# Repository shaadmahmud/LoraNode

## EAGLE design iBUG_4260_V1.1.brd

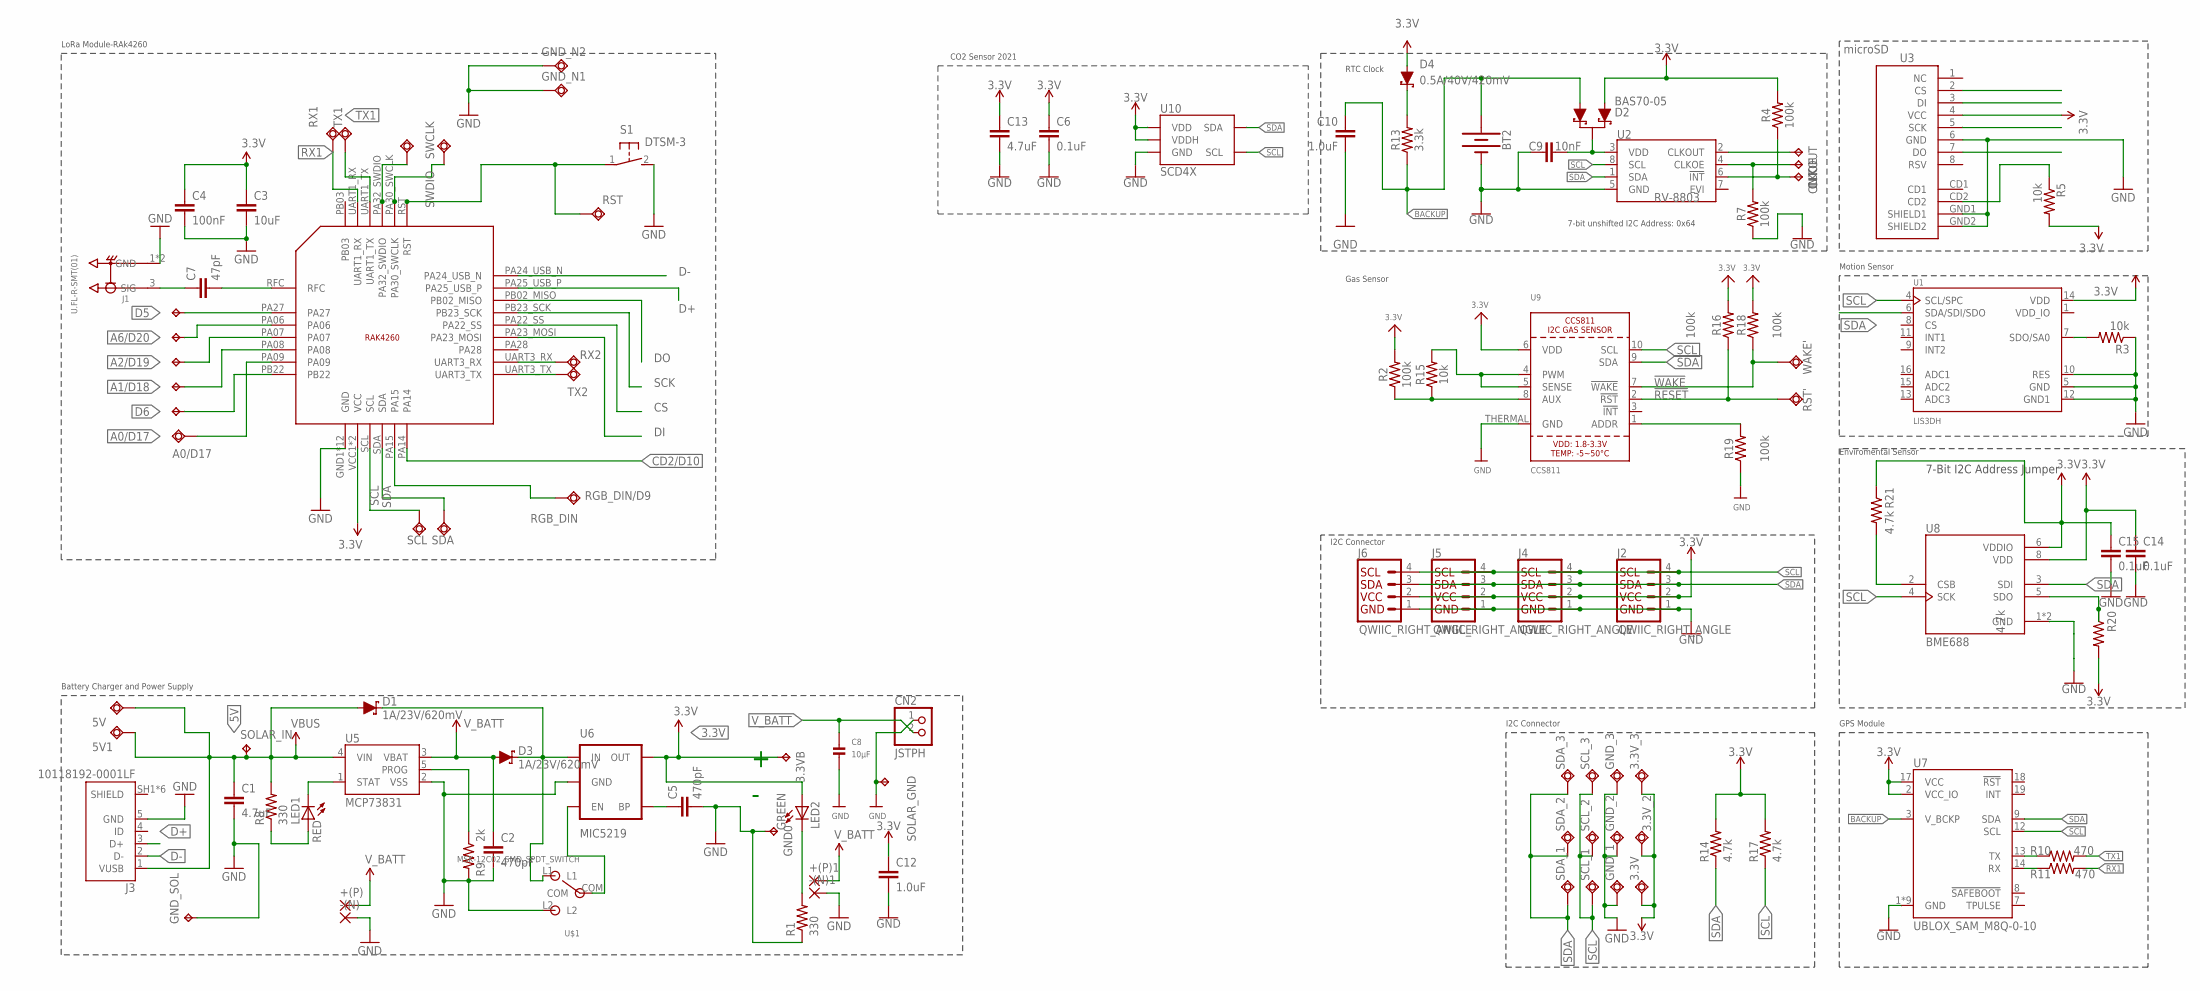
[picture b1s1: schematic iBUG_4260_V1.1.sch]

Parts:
3.3V, 3.3V_2, 3.3V_3: TPSQTP15R; TP15R
3.3VB: TPTP12SQ; TP12SQ
5V, 5V1: TPSQTP19R; TP19R
+(P), +(P)1: SMD2; SMD1,27-2,54
-(N), -(N)1: SMD2; SMD1,27-2,54
A0/D17: TPSQTP15R; TP15R
BT2: BATTERY-12MM_SMD; BATTCON_12MM
C1: 4.7uF; 0402-CAP
C2, C5: 470pF; 0402-CAP
C3: 10uF; 0402-CAP
C4: 100nF; 0402-CAP
C6, C14, C15: 0.1uF; 0603
C7: 47pF; 0402-CAP
C8: 10µF; 0805
C9: 10nF; 0603
C10, C12: 1.0uF; 0603
C13: 4.7uF; 0603
CLKOE: TPTP12R; TP12R
CLKOUT: TPTP12R; TP12R
CN2: JSTPH; JSTPH2
D1, D3: 1A/23V/620mV; SOD-323
D2: BAS70-05; SOT23-3
D4: 0.5A/40V/420mV; SOD-323
GND0: TPTP12SQ; TP12SQ
GND_1, GND_2, GND_3: TPSQTP15R; TP15R
GND_N1, GND_N2: TPSQTP19R; TP19R
GND_SOL: TPTP12SQ; TP12SQ
INT: TPTP12R; TP12R
J1: U.FL-R-SMT(01); HRS_U.FL-R-SMT(01)
J2, J4, J5, J6: QWIIC_RIGHT_ANGLE; JST04_1MM_RA
J3: 10118192-0001LF; AMPHENOL_10118192-0001LF
LED1: RED; LED-0603@1
LED2: GREEN; LED-0603@1
P0.1: TP5P5-25-13; P5-25-13
R1, R8: 330; 0402-RES
R2, R16, R18, R19: 100k; 0603@3
R3, R5: 10k; 0603-RES
R4, R7: 100k; 0603@2
R9: 2k; 0603-RES
R10, R11: 470; 0603@3
R13: 3.3k; 0603@3
R14, R17: 4.7k; 0402-RES
R15: 10k; 0603@3
R20, R21: 4.7k; 0603@1
RGB_DIN/D9: TPSQTP15R; TP15R
RST: TPSQTP19R; TP19R
RST': TPSQTP15R; TP15R
RX1, RX2: TPSQTP15R; TP15R
S1: DTSM-3
SCL: TPSQTP15R; TP15R
SCL_1, SCL_2, SCL_3: TPSQTP15R; TP15R
SDA: TPSQTP15R; TP15R
SDA_1, SDA_2, SDA_3: TPSQTP15R; TP15R
SOLAR_GND: TPTP20SQ; TP20SQ
SOLAR_IN: TPTP20SQ; TP20SQ
SWCLK: TPSQTP19R; TP19R
SWDIO: TPSQTP18R; TP18R
TX1, TX2: TPSQTP15R; TP15R
U1: LIS3DH; PQFN50P300X300X100-16N
U2: RV-8803; RV-3028
U3: microSD; MICRO-SD-SOCKET-PP
U5: MCP73831; SOT23-5
U6: MIC5219; SOT23-5
U7: UBLOX_SAM_M8Q-0-10; SAM-M8Q
U8: BME688; IC_BME688
U9: CCS811
U10: SCD4X
U$1: MSK-12C02_SMD_SPDT_SWITCH; MSK-12C02
U$3: RAK4260
WAKE': TPSQTP15R; TP15R

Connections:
3.3V: 3.3V.TP, 3.3VB.TP, 3.3V_2.TP, 3.3V_3.TP, C3.1, C4.1, C6.1, C12.1, C13.1, C14.1, C15.1, D2.1 (A), D4.A, J2.2, J4.2, J5.2, J6.2, LED2.A, R2.2, R4.2, R5.2, R14.2, R16.2, R17.2, R18.2, R20.2, R21.1, U1.14 (VDD), U3.4 (VCC), U6.5 (OUT), U7.2 (VCC_IO), U7.17 (VCC), U8.6 (VDDIO), U8.8 (VDD), U9.6 (VDD), U10.7 (VDD), U10.19 (VDDH), U$3.VCC1 (VCC), U$3.VCC2 (VCC)
5V: 5V.TP, 5V1.TP, C1.1, D1.A, J3.1 (VUSB), R8.2, SOLAR_IN.TP, U5.4 (VIN)
!INT: INT.TP, R4.1, U2.6 (!INT)
!RESET: R16.1, RST'.TP, U9.2 (!RST)
!WAKE: R18.1, U9.7 (!WAKE), WAKE'.TP
A0/D17: A0/D17.TP, U$3.PA09
A1/D18: P0.1.TP-2, U$3.PA08
A2/D19: P0.1.TP-3, U$3.PA07
A6/D20: P0.1.TP-4, U$3.PA06
BACKUP: BT2.PWR@1 (+), C10.1, D2.2 (A1), R13.1, U7.3 (V_BCKP)
CD1: R5.1, U3.CD2
CD2/D10: U$3.PA14
CLKOE: CLKOE.TP, R7.2, U2.4 (CLKOE)
CLKOUT: CLKOUT.TP, U2.2 (CLKOUT)
CS: U3.2 (CS), U$3.PA22_SS
D5: P0.1.TP-5, U$3.PA27
D6: P0.1.TP-1, U$3.PB22
D+: J3.3 (D+), U$3.PA25_USB_P
D-: J3.2 (D-), U$3.PA24_USB_N
DI: U3.3 (DI), U$3.PA23_MOSI
DO: U3.7 (DO), U$3.PB02_MISO
GND: -(N).1, -(N)1.1, BT2.GND (-), C1.2, C2.2, C3.2, C4.2, C5.2, C6.2, C8.2, C9.1, C10.2, C12.2, C13.2, C14.2, C15.2, CN2.1, GND0.TP, GND_1.TP, GND_2.TP, GND_3.TP, GND_N1.TP, GND_N2.TP, GND_SOL.TP, J1.1 (GND), J1.2 (GND), J2.1, J3.5 (GND), J4.1, J5.1, J6.1, R1.1, R3.1, R7.1, R9.2, R19.1, S1.2, SOLAR_GND.TP, U1.5 (GND), U1.10 (RES), U1.12 (GND1), U2.5 (GND), U3.6 (GND), U3.GND1 (SHIELD1), U3.GND2 (SHIELD2), U5.2 (VSS), U6.2 (GND), U7.1 (GND), U7.4 (GND), U7.5 (GND), U7.6 (GND), U7.10 (GND), U7.11 (GND), U7.15 (GND), U7.16 (GND), U7.20 (GND), U8.1 (GND), U8.7 (GND), U9.THERMAL (GND), U10.6 (GND), U10.20 (GND), U10.CP (GND), U$1.L2, U$3.GND1 (GND), U$3.GND3 (GND), U$3.GND10 (GND), U$3.GND17 (GND), U$3.GND18 (GND), U$3.GND28 (GND), U$3.GND35 (GND), U$3.GND36 (GND), U$3.GND37 (GND), U$3.GND38 (GND), U$3.GND39 (GND), U$3.GND40 (GND)
unnamed: LED2.C, R1.2
unnamed: D1.C, D3.C, U6.1 (IN), U$1.L1
unnamed: C7.1, J1.3 (SIG)
unnamed: R9.1, U5.5 (PROG)
unnamed: U6.3 (EN), U$1.COM
unnamed: C7.2, U$3.RFC
unnamed: C9.2, D2.3 (C), U2.3 (VDD)
unnamed: SWDIO.TP, U$3.PA32_SWDIO
unnamed: R15.2, U9.4 (PWM), U9.5 (SENSE)
unnamed: R2.1, R15.1, U9.8 (AUX)
unnamed: LED1.A, R8.1
unnamed: LED1.C, U5.1 (STAT)
unnamed: R19.2, U9.1 (ADDR)
unnamed: C5.1, U6.4 (BP)
unnamed: RX2.TP, U$3.UART3_RX
unnamed: R3.2, U1.7 (SDO/SA0)
unnamed: SWCLK.TP, U$3.PA30_SWCLK
unnamed: R20.1, U8.5 (SDO)
unnamed: TX2.TP, U$3.UART3_TX
unnamed: D4.C, R13.2
unnamed: R21.2, U8.2 (CSB)
RGB_DIN: RGB_DIN/D9.TP, U$3.PA15
RST: RST.TP, S1.1, U$3.RST
RX1: R11.2, RX1.TP, U$3.UART1_RX
RXLV: R11.1, U7.14 (RX)
SCK: U3.5 (SCK), U$3.PB23_SCK
SCL: J2.4, J4.4, J5.4, J6.4, R17.1, SCL.TP, SCL_1.TP, SCL_2.TP, SCL_3.TP, U1.4 (SCL/SPC), U2.8 (SCL), U7.12 (SCL), U8.4 (SCK), U9.10 (SCL), U10.9 (SCL), U$3.SCL
SDA: J2.3, J4.3, J5.3, J6.3, R14.1, SDA.TP, SDA_1.TP, SDA_2.TP, SDA_3.TP, U1.6 (SDA/SDI/SDO), U2.1 (SDA), U7.9 (SDA), U8.3 (SDI), U9.9 (SDA), U10.10 (SDA), U$3.SDA
TX1: R10.2, TX1.TP, U$3.UART1_TX
TXLV: R10.1, U7.13 (TX)
VDD_IO: U1.1 (VDD_IO)
V_BATT: +(P).1, +(P)1.1, C2.1, C8.1, CN2.2, D3.A, U5.3 (VBAT)

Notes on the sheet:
Battery Charger and Power Supply
7-bit unshifted I2C Address: 0x64
7-Bit I2C Address Jumper
GPS Module
Enviromental Sensor
Motion Sensor
I2C Connector
RTC Clock
LoRa Module-RAk4260
CO2 Sensor 2021
Gas Sensor

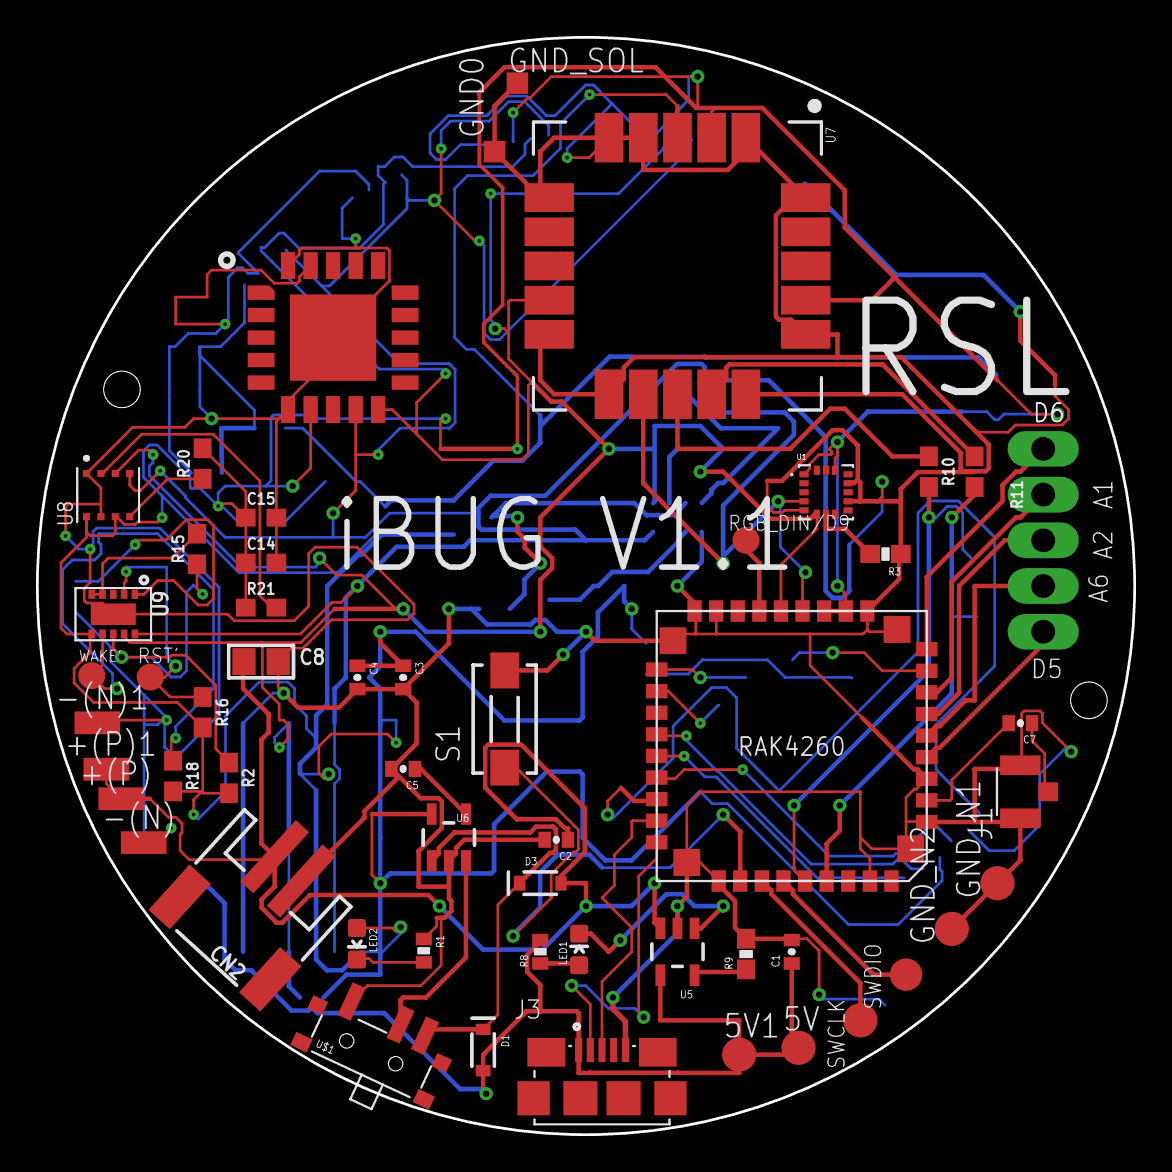
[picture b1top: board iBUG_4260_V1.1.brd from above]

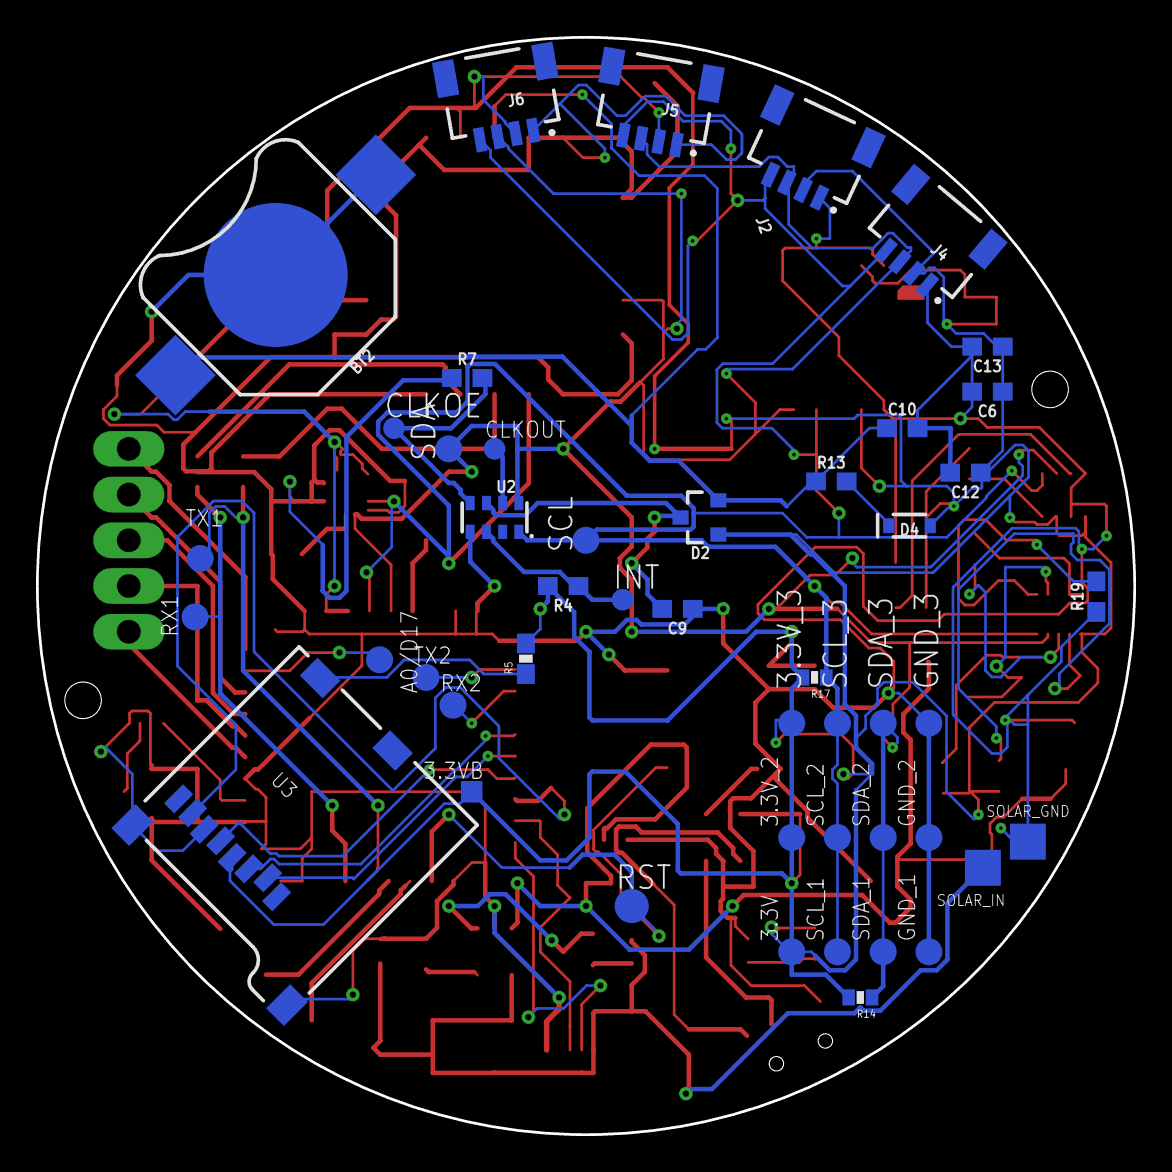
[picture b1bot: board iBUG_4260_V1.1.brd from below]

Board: 2 copper layers, 61.0 x 61.0 mm, 101 parts (47 on the bottom side), 52 nets.

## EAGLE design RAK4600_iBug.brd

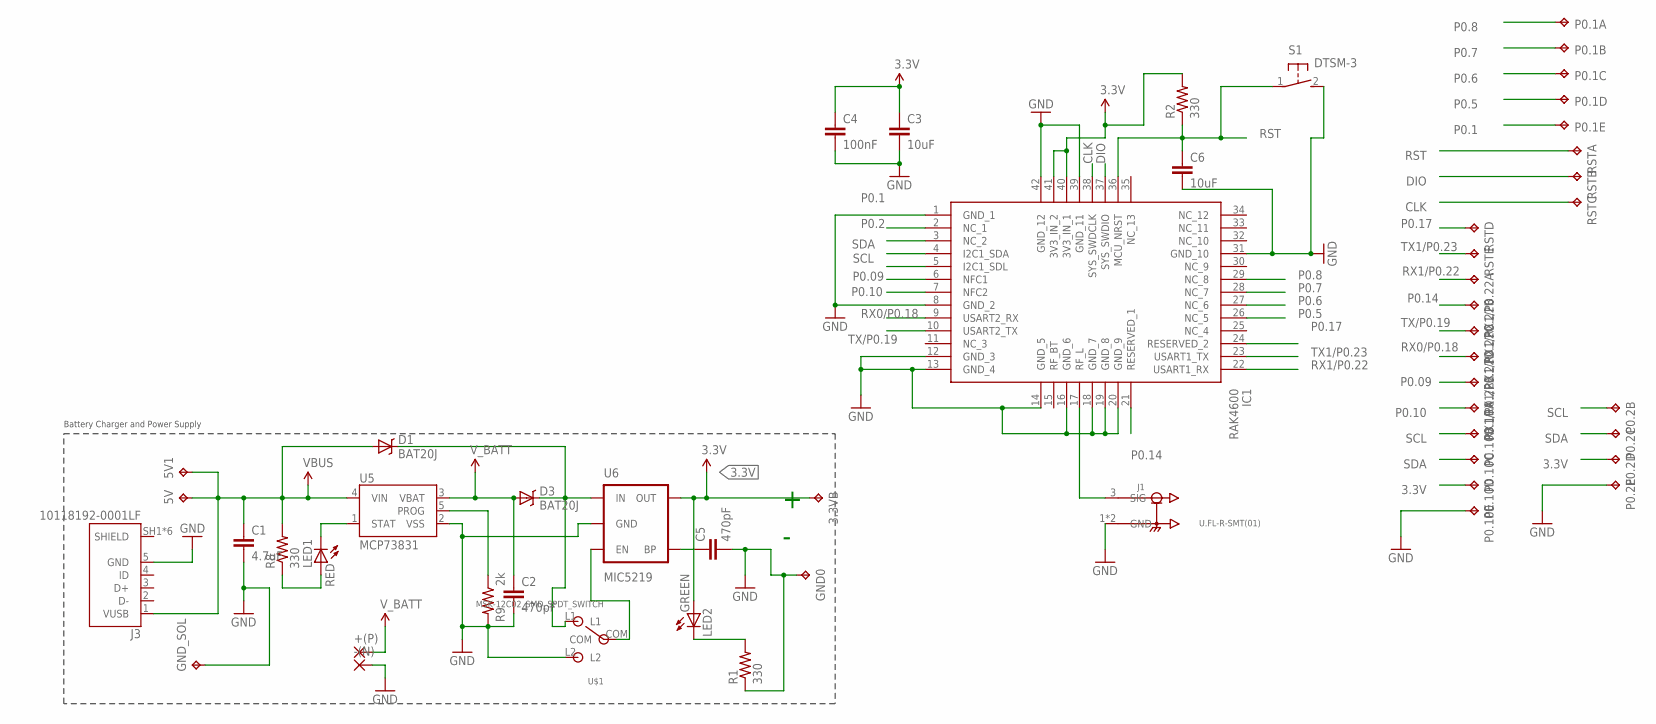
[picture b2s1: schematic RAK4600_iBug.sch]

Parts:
3.3VB, 5V, 5V1: TPTP12SQ; TP12SQ
+(P): SMD2; SMD1,27-2,54
-(N): SMD2; SMD1,27-2,54
C1: 4.7uF; 0402-CAP
C2, C5: 470pF; 0402-CAP
C3, C6: 10uF; 0402-CAP
C4: 100nF; 0402-CAP
D1, D3: BAT20J; SOD-323
GND0: TPTP12SQ; TP12SQ
GND_SOL: TPTP12SQ; TP12SQ
IC1: RAK4600
J1: U.FL-R-SMT(01); HRS_U.FL-R-SMT(01)
J3: 10118192-0001LF; AMPHENOL_10118192-0001LF
LED1: RED; LED-0603
LED2: GREEN; LED-0603
P0.1, P0.2, P0.10: TP5P5-25-13; P5-25-13
R1, R2, R8: 330; 0402-RES
R9: 2k; 0603-RES
RST: TP5P5-25-13; P5-25-13
RX1/P0.22: TP5P5-25-13; P5-25-13
S1: DTSM-3
U5: MCP73831; SOT23-5
U6: MIC5219; SOT23-5
U$1: MSK-12C02_SMD_SPDT_SWITCH; MSK-12C02

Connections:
3.3V: 3.3VB.TP, C3.1, C4.1, IC1.40 (3V3_IN_1), IC1.41 (3V3_IN_2), LED2.A, P0.2.TP-4, P0.10.TP-4, R2.2, U6.5 (OUT)
5V: 5V.TP, 5V1.TP, C1.1, D1.A, J3.1 (VUSB), R8.2, U5.4 (VIN)
CLK: IC1.38 (SYS_SWDCLK), RST.TP-3
DIO: IC1.37 (SYS_SWDIO), RST.TP-2
GND: -(N).1, C1.2, C2.2, C3.2, C4.2, C5.2, C6.2, GND0.TP, GND_SOL.TP, IC1.1 (GND_1), IC1.8 (GND_2), IC1.12 (GND_3), IC1.13 (GND_4), IC1.14 (GND_5), IC1.16 (GND_6), IC1.18 (GND_7), IC1.19 (GND_8), IC1.20 (GND_9), IC1.31 (GND_10), IC1.39 (GND_11), IC1.42 (GND_12), J1.1 (GND), J1.2 (GND), J3.5 (GND), P0.2.TP-5, P0.10.TP-5, R1.1, R9.2, S1.2, U5.2 (VSS), U6.2 (GND), U$1.L2
unnamed: LED2.C, R1.2
unnamed: D1.C, D3.C, U6.1 (IN), U$1.L1
unnamed: IC1.17 (RF_L), J1.3 (SIG)
unnamed: R9.1, U5.5 (PROG)
unnamed: U6.3 (EN), U$1.COM
unnamed: LED1.A, R8.1
unnamed: LED1.C, U5.1 (STAT)
unnamed: C5.1, U6.4 (BP)
P0.1: IC1.2 (NC_1), P0.1.TP-5
P0.2: IC1.3 (NC_2)
P0.5: IC1.26 (NC_5), P0.1.TP-4
P0.6: IC1.27 (NC_6), P0.1.TP-3
P0.7: IC1.28 (NC_7), P0.1.TP-2
P0.8: IC1.29 (NC_8), P0.1.TP-1
P0.09: IC1.6 (NFC1), RX1/P0.22.TP-5
P0.10: IC1.7 (NFC2), P0.10.TP-1
P0.14: IC1.21 (RESERVED_1), RX1/P0.22.TP-2
P0.17: IC1.24 (RESERVED_2), RST.TP-4
RST: C6.1, IC1.36 (MCU_NRST), R2.1, RST.TP-1, S1.1
RX0/P0.18: IC1.9 (USART2_RX), RX1/P0.22.TP-4
RX1/P0.22: IC1.22 (USART1_RX), RX1/P0.22.TP-1
SCL: IC1.5 (I2C1_SDL), P0.2.TP-2, P0.10.TP-2
SDA: IC1.4 (I2C1_SDA), P0.2.TP-3, P0.10.TP-3
TX1/P0.23: IC1.23 (USART1_TX), RST.TP-5
TX/P0.19: IC1.10 (USART2_TX), RX1/P0.22.TP-3
V_BATT: +(P).1, C2.1, D3.A, U5.3 (VBAT)

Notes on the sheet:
Battery Charger and Power Supply

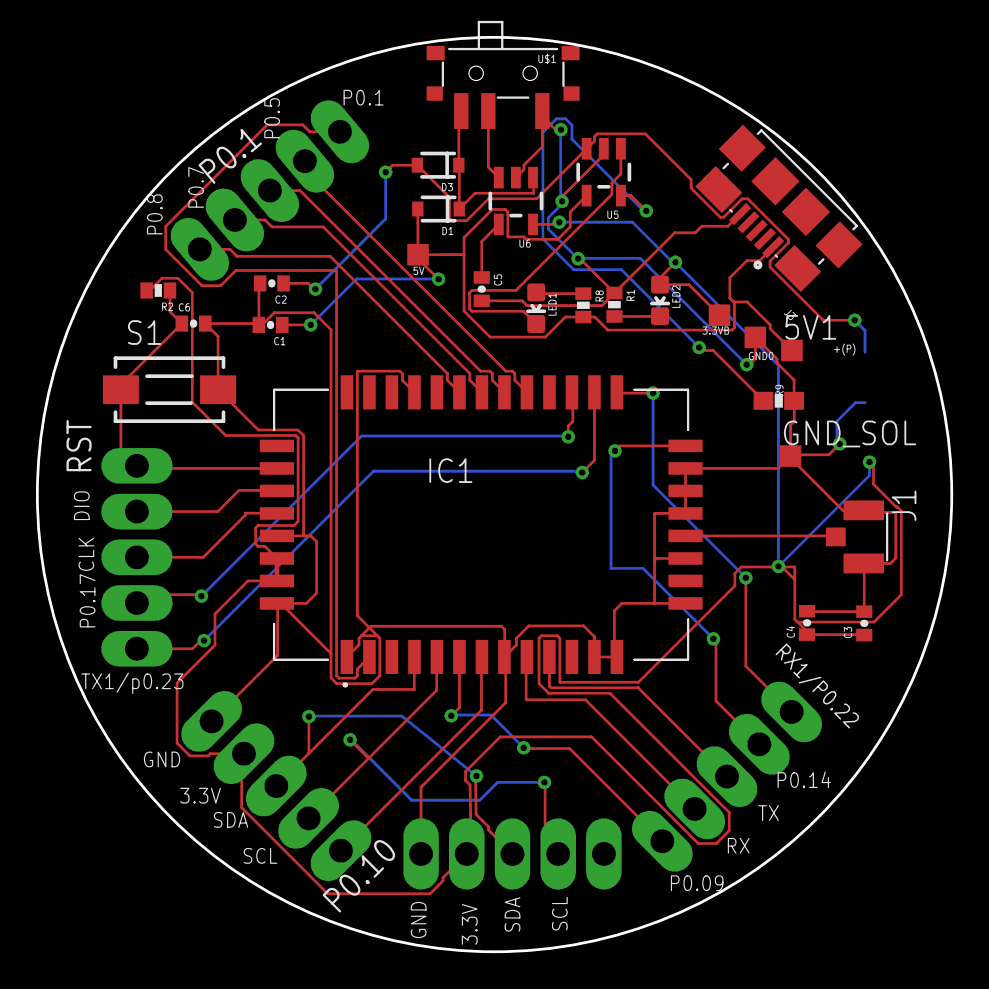
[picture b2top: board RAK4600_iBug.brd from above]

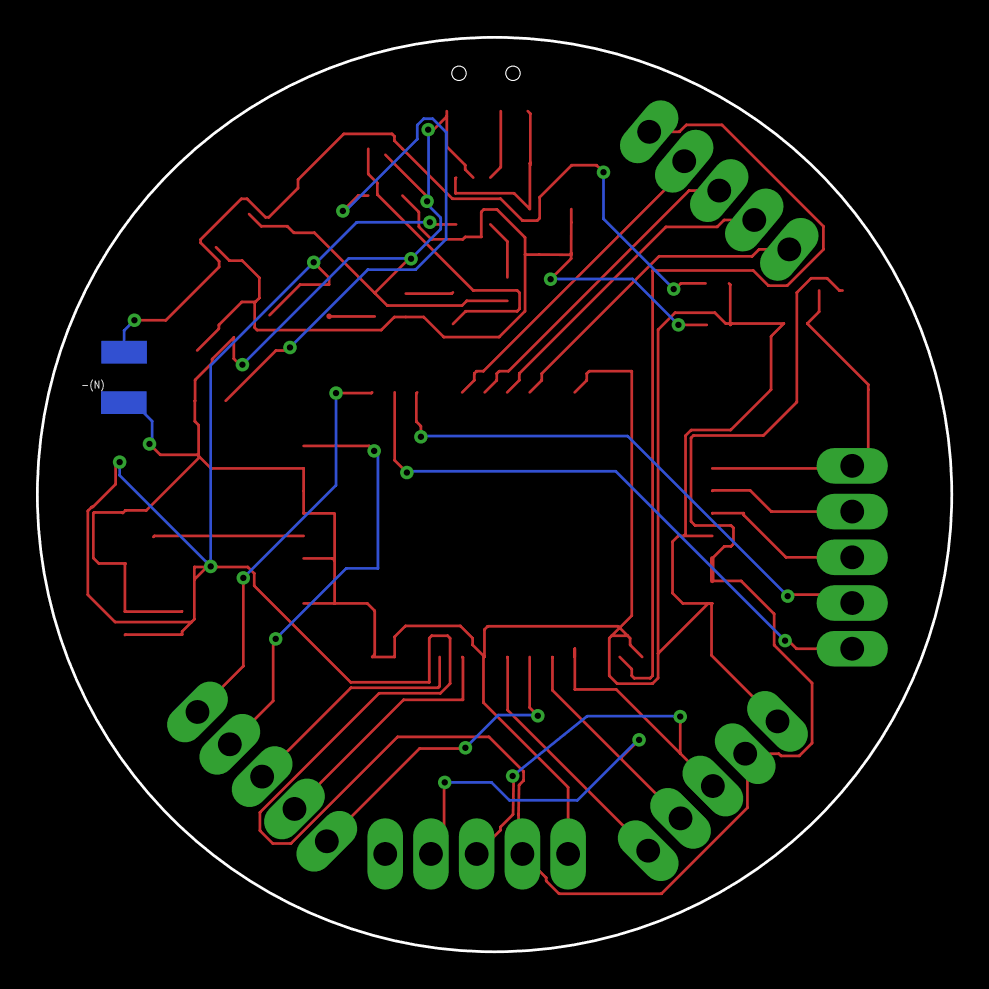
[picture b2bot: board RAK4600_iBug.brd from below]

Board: 2 copper layers, 50.8 x 50.8 mm, 33 parts (2 on the bottom side), 30 nets.

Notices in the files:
parts and their libraries:
SparkFun-Passives: Licensing: CC v3.0 Share-Alike You are welcome to use this library for commercial purposes.
SparkFun-DiscreteSemi: Licensing: Creative Commons ShareAlike 4.0 International - https://creativecommons.org/licenses/by-sa/4.0
